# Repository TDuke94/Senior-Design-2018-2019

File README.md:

# Senior-Design-2018-2019
UCF ECE Department Senior Design Group 12

Group Members:
  Fredlin Durand
  Timothy Duke
  Daniel Gutierrez
  Linnette Martinez

This is the code and code issue repository for our Senior Design Project

The goal of this project is the development and prototype implementation of IMU based motion tracking system.

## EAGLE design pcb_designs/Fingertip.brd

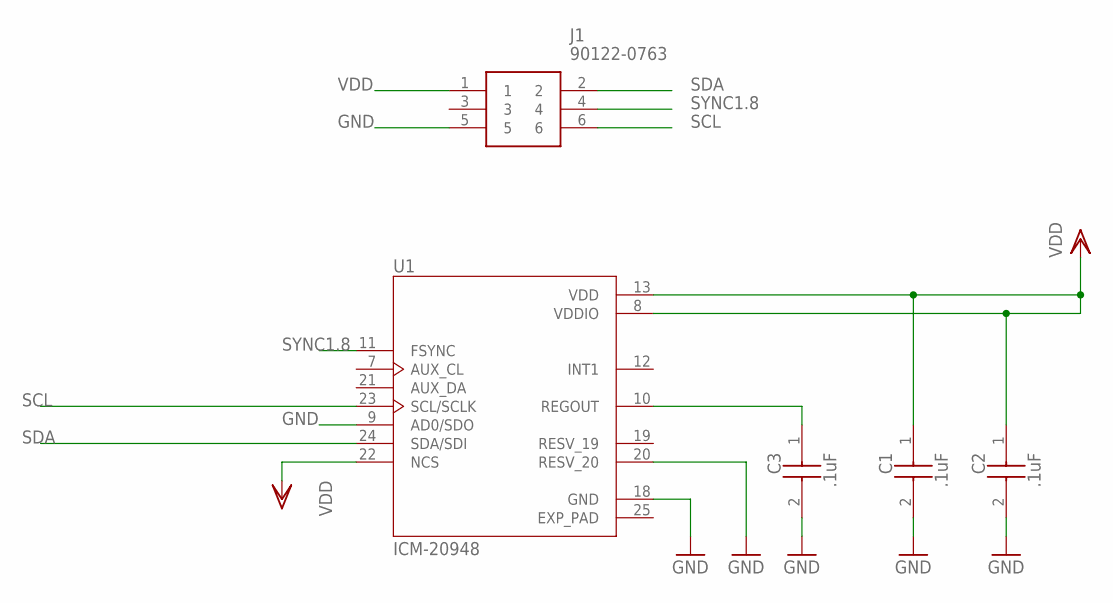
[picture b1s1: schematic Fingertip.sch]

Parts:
C1, C2, C3: .1uF; CAPC2012X88N
J1: 90122-0763; SHDR6W90P254_2X3_762X605X684P
U1: ICM-20948; QFN40P300X300X105-25N

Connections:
EXP_PAD: U1.25 (EXP_PAD)
GND: C1.2, C2.2, C3.2, J1.5, U1.9 (AD0/SDO), U1.18 (GND), U1.20 (RESV_20)
unnamed: C3.1, U1.10 (REGOUT)
SCL: J1.6, U1.23 (SCL/SCLK)
SDA: J1.2, U1.24 (SDA/SDI)
SYNC1.8: J1.4, U1.11 (FSYNC)
VDD: C1.1, C2.1, J1.1, U1.8 (VDDIO), U1.13 (VDD), U1.22 (NCS)

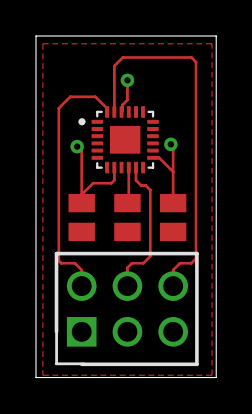
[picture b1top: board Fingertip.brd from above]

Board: 2 copper layers, 10.0 x 19.0 mm, 5 parts (0 on the bottom side), 6 nets.

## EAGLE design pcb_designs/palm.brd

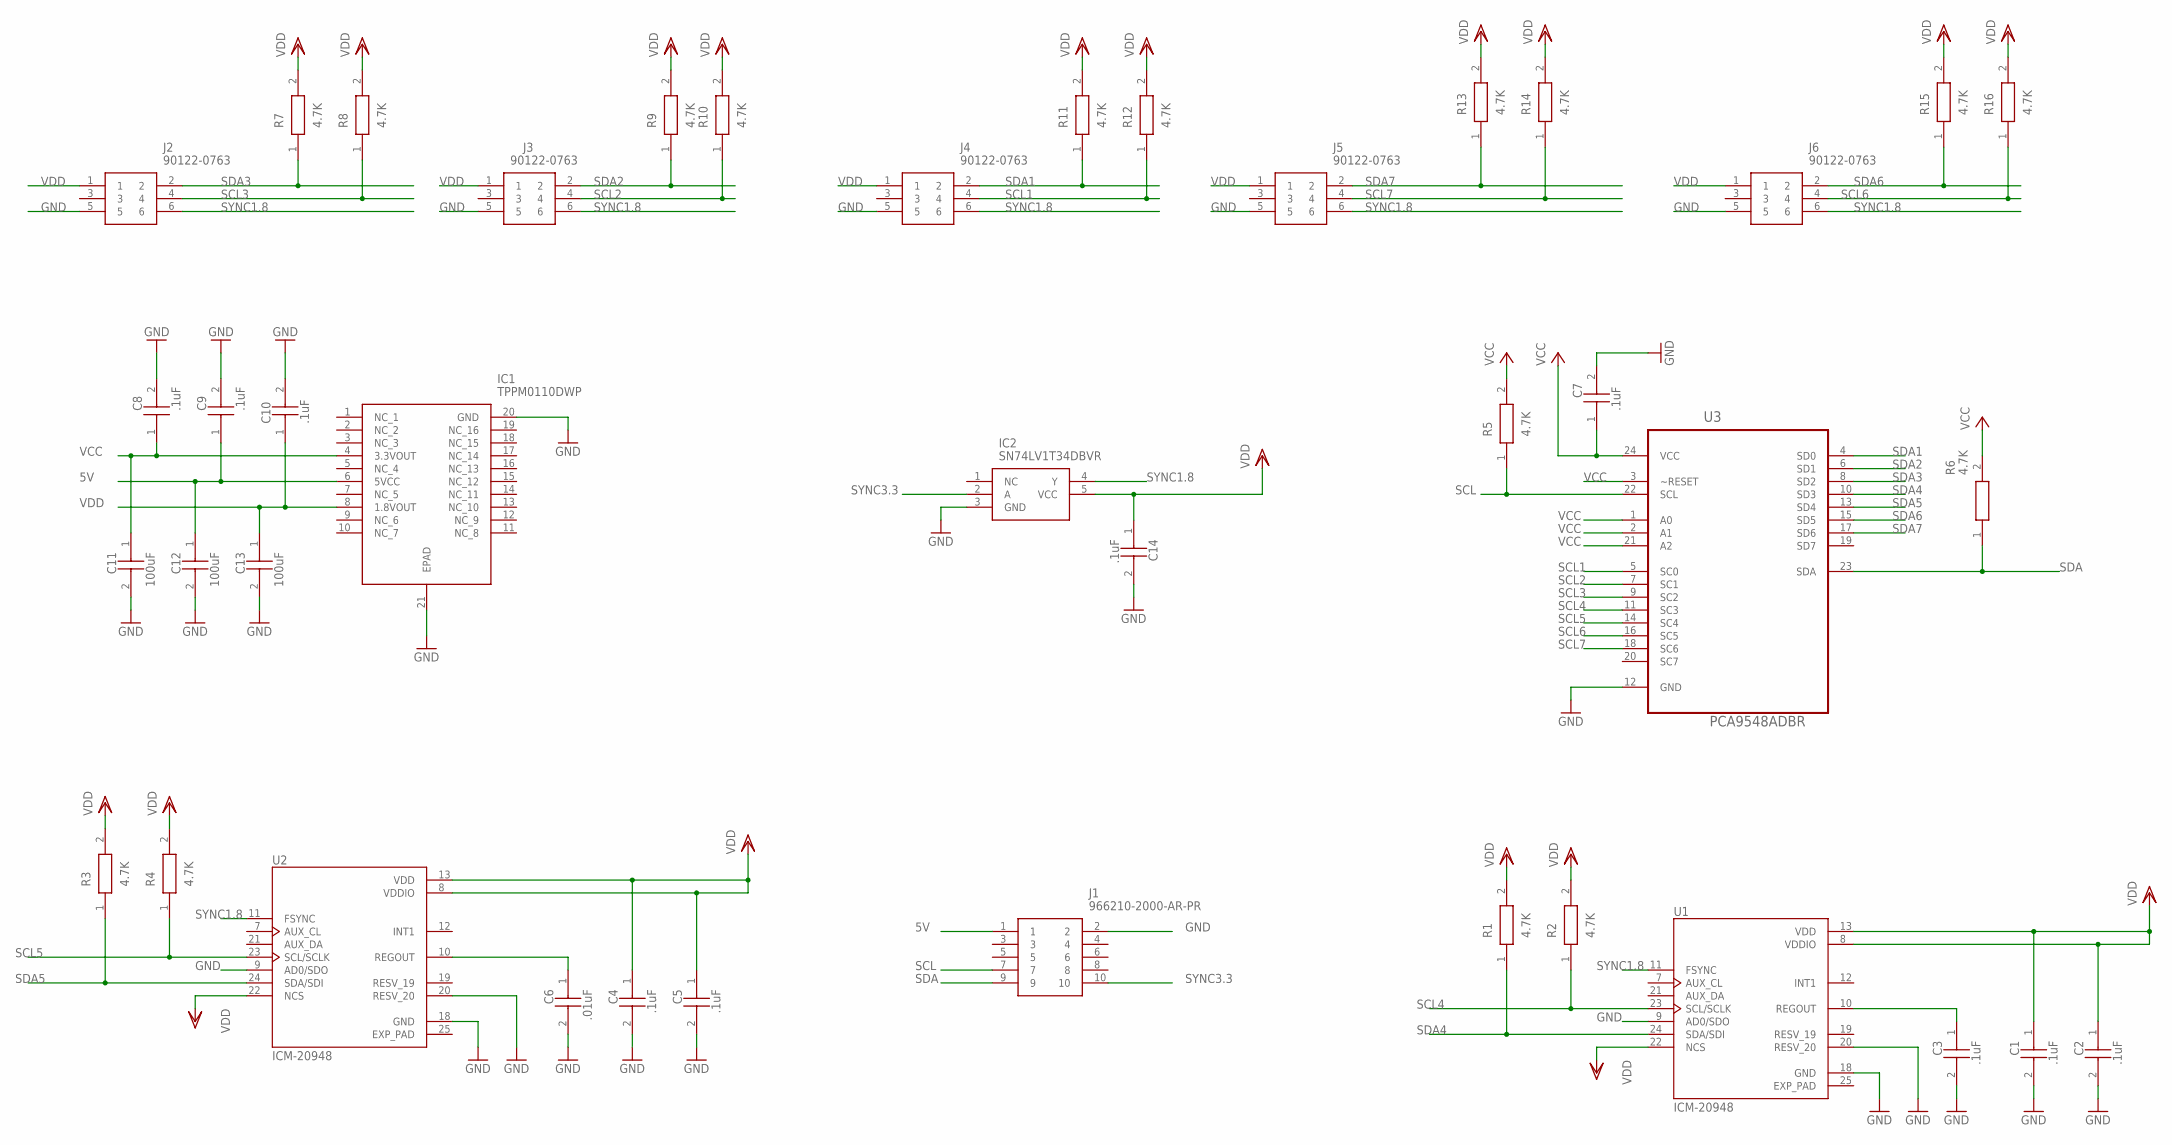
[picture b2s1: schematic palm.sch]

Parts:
C1, C2, C3, C4, C5, C7, C8, C9, C10, C14: .1uF; CAPC2012X88N
C6: .01uF; CAPC2012X88N
C11, C12, C13: 100uF; CAPC3225X279N
IC1: TPPM0110DWP; SOIC127P1040X265-21N
IC2: SN74LV1T34DBVR; SOT95P280X145-5N
J1: 966210-2000-AR-PR
J2, J3, J4, J5, J6: 90122-0763; SHDR6W90P254_2X3_762X605X684P
R1, R2, R3, R4, R5, R6, R7, R8, R9, R10, R11, R12, R13, R14, R15, R16: 4.7K; RESC3216X60N
U1, U2: ICM-20948; QFN40P300X300X105-25N
U3: PCA9548ADBR; SOP65P780X200-24N

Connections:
5V: C9.1, C12.1 (C1), IC1.6 (5VCC), J1.1
EXP_PAD: U1.25 (EXP_PAD), U2.25 (EXP_PAD)
GND: C1.2, C2.2, C3.2, C4.2, C5.2, C6.2, C7.2, C8.2, C9.2, C10.2, C11.2 (C2), C12.2 (C2), C13.2 (C2), C14.2, IC1.20 (GND), IC1.21 (EPAD), IC2.3 (GND), J1.2, J2.5, J3.5, J4.5, J5.5, J6.5, U1.9 (AD0/SDO), U1.18 (GND), U1.20 (RESV_20), U2.9 (AD0/SDO), U2.18 (GND), U2.20 (RESV_20), U3.12 (GND)
unnamed: C6.1, U2.10 (REGOUT)
unnamed: C3.1, U1.10 (REGOUT)
SCL: J1.7, R5.1, U3.22 (SCL)
SCL1: J4.4, R12.1, U3.5 (SC0)
SCL2: J3.4, R10.1, U3.7 (SC1)
SCL3: J2.4, R8.1, U3.9 (SC2)
SCL4: R2.1, U1.23 (SCL/SCLK), U3.11 (SC3)
SCL5: R4.1, U2.23 (SCL/SCLK), U3.14 (SC4)
SCL6: J6.4, R16.1, U3.16 (SC5)
SCL7: J5.4, R14.1, U3.18 (SC6)
SDA: J1.9, R6.1, U3.23 (SDA)
SDA1: J4.2, R11.1, U3.4 (SD0)
SDA2: J3.2, R9.1, U3.6 (SD1)
SDA3: J2.2, R7.1, U3.8 (SD2)
SDA4: R1.1, U1.24 (SDA/SDI), U3.10 (SD3)
SDA5: R3.1, U2.24 (SDA/SDI), U3.13 (SD4)
SDA6: J6.2, R15.1, U3.15 (SD5)
SDA7: J5.2, R13.1, U3.17 (SD6)
SYNC1.8: IC2.4 (Y), J2.6, J3.6, J4.6, J5.6, J6.6, U1.11 (FSYNC), U2.11 (FSYNC)
SYNC3.3: IC2.2 (A), J1.10
VCC: C7.1, C8.1, C11.1 (C1), IC1.4 (3.3VOUT), R5.2, R6.2, U3.1 (A0), U3.2 (A1), U3.3 (~RESET), U3.21 (A2), U3.24 (VCC)
VDD: C1.1, C2.1, C4.1, C5.1, C10.1, C13.1 (C1), C14.1, IC1.8 (1.8VOUT), IC2.5 (VCC), J2.1, J3.1, J4.1, J5.1, J6.1, R1.2, R2.2, R3.2, R4.2, R7.2, R8.2, R9.2, R10.2, R11.2, R12.2, R13.2, R14.2, R15.2, R16.2, U1.8 (VDDIO), U1.13 (VDD), U1.22 (NCS), U2.8 (VDDIO), U2.13 (VDD), U2.22 (NCS)

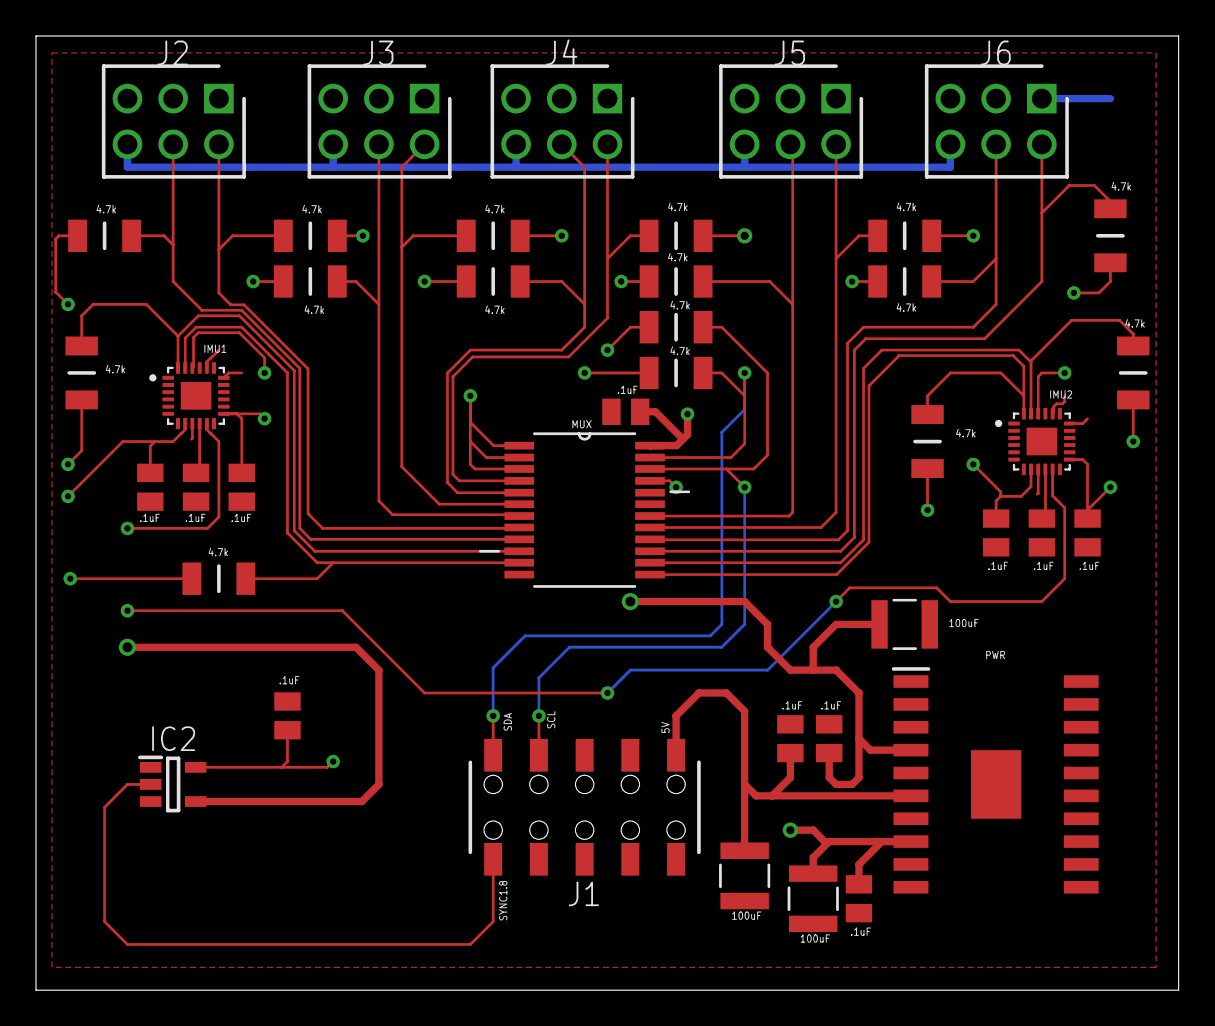
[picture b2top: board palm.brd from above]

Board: 2 copper layers, 63.5 x 53.0 mm, 41 parts (0 on the bottom side), 25 nets.

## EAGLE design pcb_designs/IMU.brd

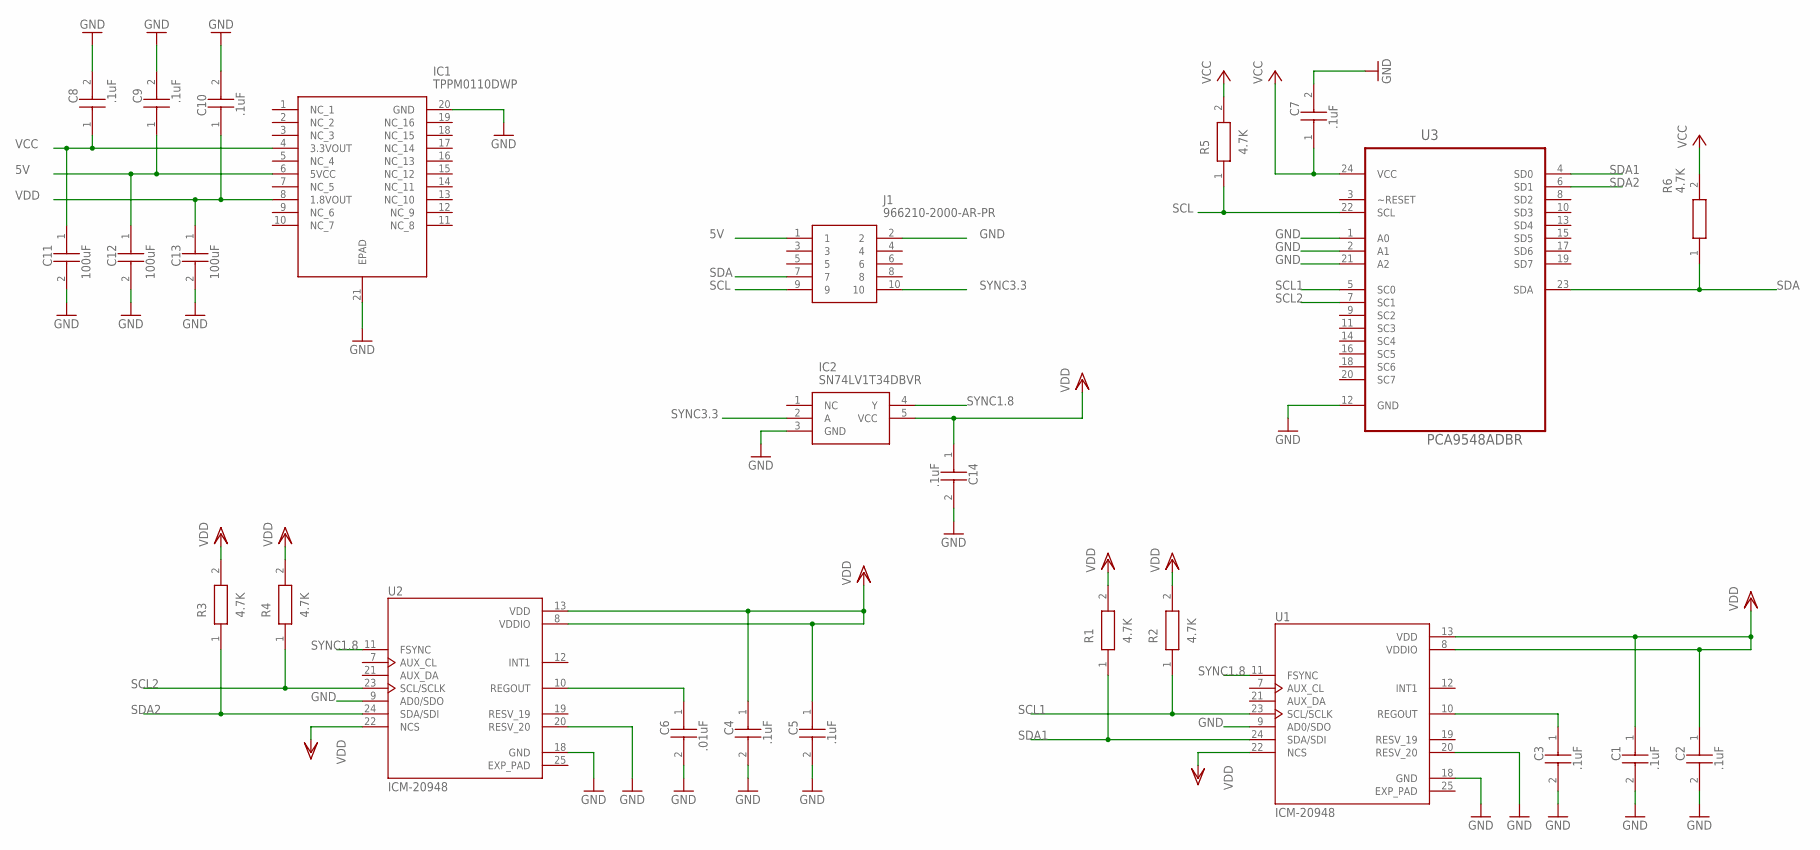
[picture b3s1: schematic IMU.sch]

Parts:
C1, C2, C3, C4, C5, C7, C8, C9, C10, C14: .1uF; CAPC2012X88N
C6: .01uF; CAPC2012X88N
C11, C12, C13: 100uF; CAPC3225X279N
IC1: TPPM0110DWP; SOIC127P1040X265-21N
IC2: SN74LV1T34DBVR; SOT95P280X145-5N
J1: 966210-2000-AR-PR
R1, R2, R3, R4, R5, R6: 4.7K; RESC3216X60N
U1, U2: ICM-20948; QFN40P300X300X105-25N
U3: PCA9548ADBR; SOP65P780X200-24N

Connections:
5V: C9.1, C12.1 (C1), IC1.6 (5VCC), J1.1
EXP_PAD: U1.25 (EXP_PAD), U2.25 (EXP_PAD)
GND: C1.2, C2.2, C3.2, C4.2, C5.2, C6.2, C7.2, C8.2, C9.2, C10.2, C11.2 (C2), C12.2 (C2), C13.2 (C2), C14.2, IC1.20 (GND), IC1.21 (EPAD), IC2.3 (GND), J1.2, U1.9 (AD0/SDO), U1.18 (GND), U1.20 (RESV_20), U2.9 (AD0/SDO), U2.18 (GND), U2.20 (RESV_20), U3.1 (A0), U3.2 (A1), U3.12 (GND), U3.21 (A2)
unnamed: C6.1, U2.10 (REGOUT)
unnamed: C3.1, U1.10 (REGOUT)
SCL: J1.9, R5.1, U3.22 (SCL)
SCL1: R2.1, U1.23 (SCL/SCLK), U3.5 (SC0)
SCL2: R4.1, U2.23 (SCL/SCLK), U3.7 (SC1)
SDA: J1.7, R6.1, U3.23 (SDA)
SDA1: R1.1, U1.24 (SDA/SDI), U3.4 (SD0)
SDA2: R3.1, U2.24 (SDA/SDI), U3.6 (SD1)
SYNC1.8: IC2.4 (Y), U1.11 (FSYNC), U2.11 (FSYNC)
SYNC3.3: IC2.2 (A), J1.10
VCC: C7.1, C8.1, C11.1 (C1), IC1.4 (3.3VOUT), R5.2, R6.2, U3.24 (VCC)
VDD: C1.1, C2.1, C4.1, C5.1, C10.1, C13.1 (C1), C14.1, IC1.8 (1.8VOUT), IC2.5 (VCC), R1.2, R2.2, R3.2, R4.2, U1.8 (VDDIO), U1.13 (VDD), U1.22 (NCS), U2.8 (VDDIO), U2.13 (VDD), U2.22 (NCS)

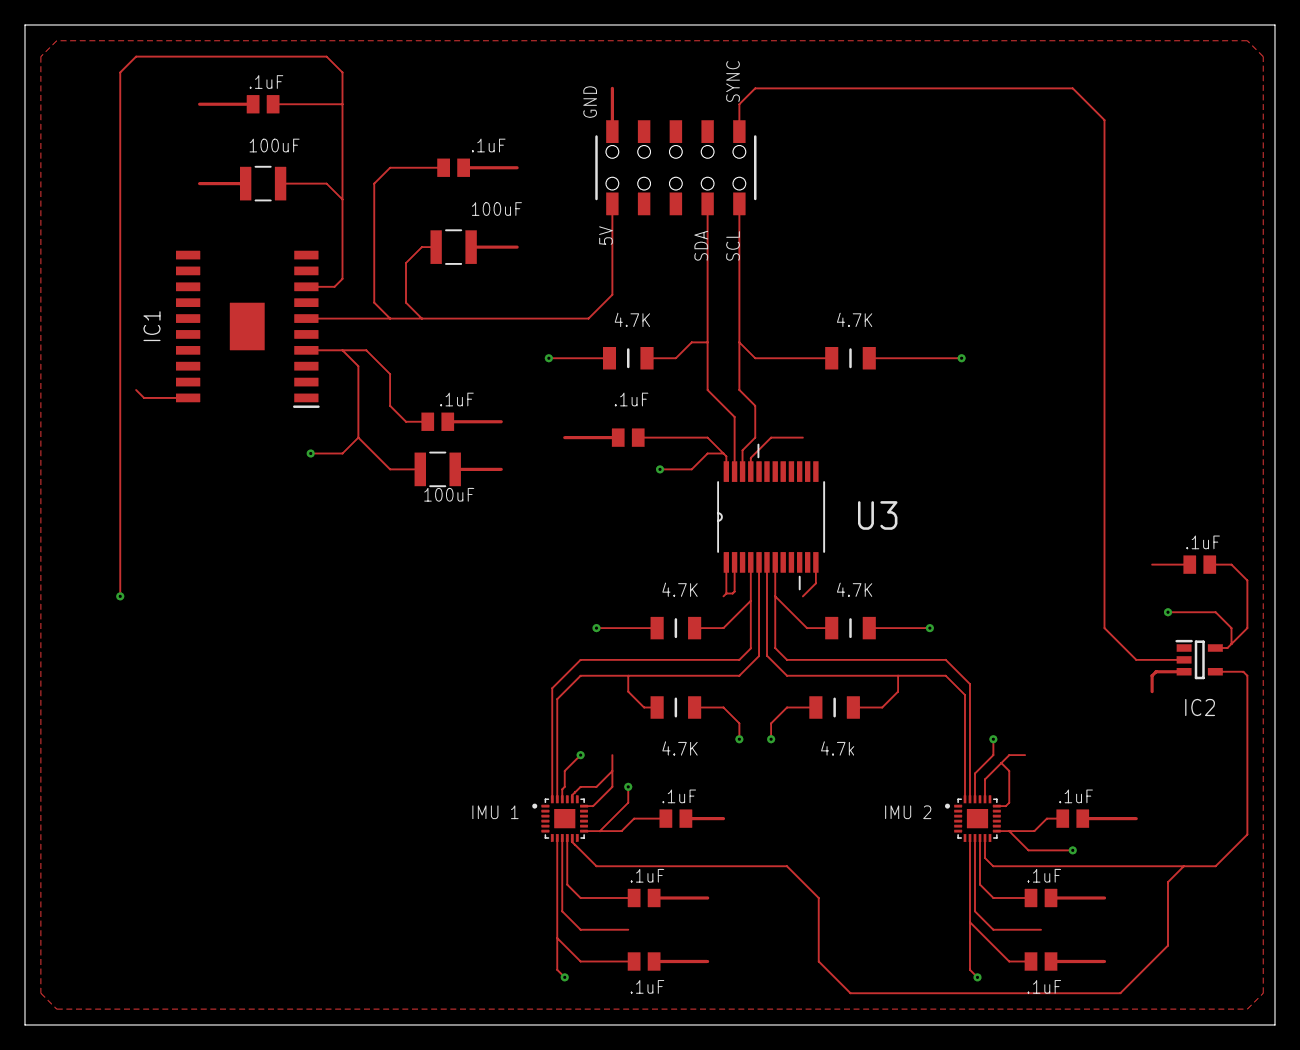
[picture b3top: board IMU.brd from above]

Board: 2 copper layers, 100.0 x 80.0 mm, 26 parts (0 on the bottom side), 15 nets.

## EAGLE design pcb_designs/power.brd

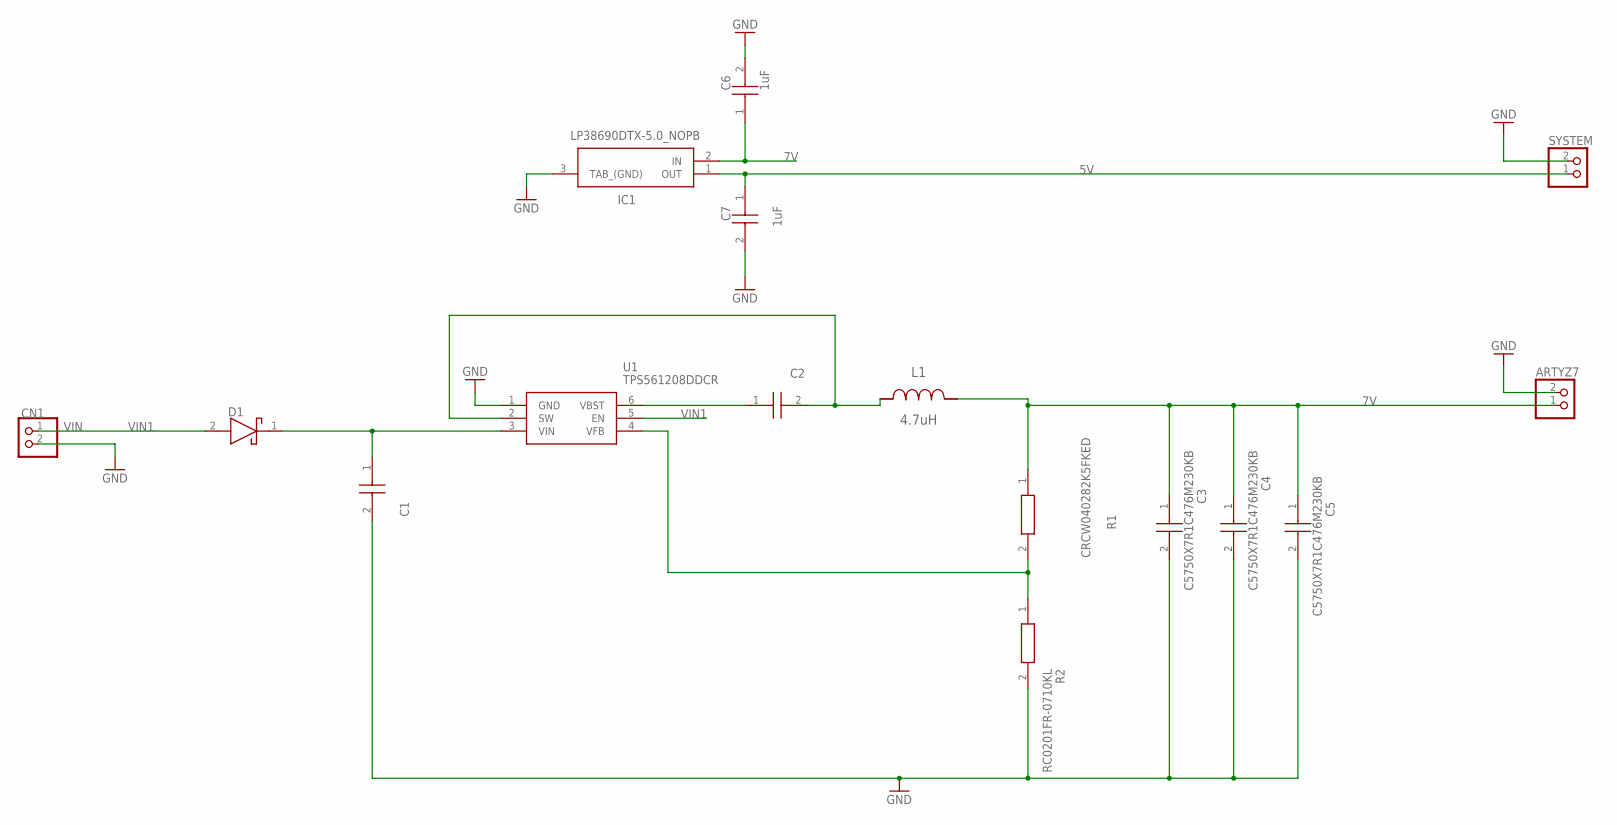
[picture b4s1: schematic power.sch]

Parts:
ARTYZ7: JST_2PIN-SMT-RA; JST-PH-2-SMT-RA
C1: 593D226X9025D2TE3; CAPPM7343X310N
C2: C0603C104Z3VACTU; CAPC1608X90N
C3, C4, C5: C5750X7R1C476M230KB; CAPC5750X250N
C6, C7: 1uF; CAPC1608X80N
CN1: JST_2PIN-SMT-RA; JST-PH-2-SMT-RA
D1: NRVB120VLSFT1G; SODFL3616X98N
IC1: LP38690DTX-5.0_NOPB; LM78M05CDT
L1: 4.7uH; SLF7045
R1: CRCW040282K5FKED; RESC1005X40N
R2: RC0201FR-0710KL; RESC0603X26N
SYSTEM: JST_2PIN-SMT-RA; JST-PH-2-SMT-RA
U1: TPS561208DDCR; SOT95P280X110-6N

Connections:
5V: C7.1, IC1.1 (OUT), SYSTEM.1 (2)
7V: ARTYZ7.1 (2), C3.1, C4.1, C5.1, C6.1, IC1.2 (IN), L1.2, R1.1
GND: ARTYZ7.2 (1), C1.2 (-), C3.2, C4.2, C5.2, C6.2, C7.2, CN1.2 (1), IC1.3 (TAB_(GND)), R2.2, SYSTEM.2 (1), U1.1 (GND)
unnamed: C2.1, U1.6 (VBST)
unnamed: C2.2, L1.1, U1.2 (SW)
unnamed: R1.2, R2.1, U1.4 (VFB)
VIN: CN1.1 (2), D1.2 (A)
VIN1: C1.1 (+), D1.1 (K), U1.3 (VIN), U1.5 (EN)

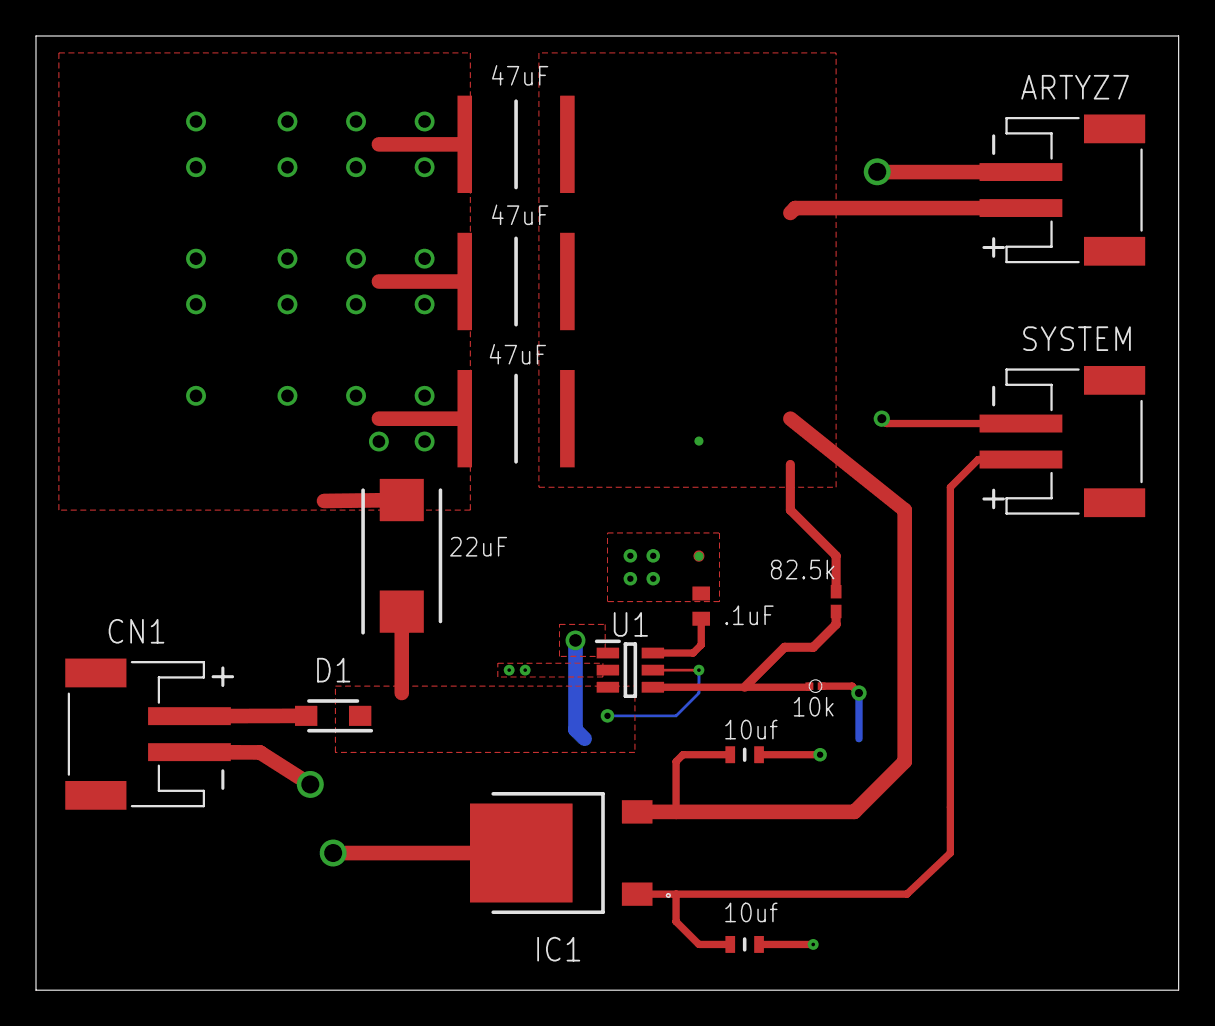
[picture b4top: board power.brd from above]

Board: 2 copper layers, 63.5 x 53.0 mm, 16 parts (0 on the bottom side), 8 nets.

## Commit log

2018-11-14 Upload of SD Card Image
    Upload of the first SD card image to use for initial board testing
2018-11-14 New SD Card Image
2018-12-21 This is some basic code demonstrating the usage of a queue buffer sending data from one task to another
2018-12-21 I2C Initial
    Initial upload of I2C code under development.
2018-12-28 Arty-Z7 Initial Upload
2018-12-28 Queue Test Funcitonal v0
2019-01-14 This is some preliminary code written in C that tries to take data and perform calculations that will provide key data
2019-01-15 Updated Queue Design, Bugs Remain
2019-01-19 This is the early eversion of implementing the math functions that will be used for IMIU Data manipulation.
2019-01-19 ~minor change~
2019-01-19 new Queue Version and I2C on Zynq
2019-01-19 MSP430 I2C update, Talks to Zynq
2019-01-19 Update of Zynq I2C capabilities
2019-01-20 I2C Driver Update
2019-01-23 this update contains a more structured and well defined Math Library that will allow for easier use on Queue Tasks. Code cleanup and comments still needs to be workedd on
2019-02-15 Modified the Math Library Functions in Data Manipulation
2019-02-15 I2C to Zynq Update
2019-03-08 Update with functioning pipeline and SPI (marginal)
2019-03-11 SPI refresh
2019-03-26 Bluetooth/SPI Integration Code Update
2019-03-26 fixing things
2019-03-26 this might have fixed the uploading
2019-03-29 ICM 20948 and pipeline updates
2019-03-29 Physical models from Onshape and 3D models from Maya
2019-03-29 eagle designs
2019-04-02 MSP430 with two IMUs
2019-04-02 SPI code
2019-04-02 SPI and BT updates - slight code clean
2019-04-04 msp forgotten file :'(
2019-04-04 fixing BT comm to support AA filtering from SPI
2019-04-04 SPI filter addition
2019-04-05 i2c update
2019-04-10 uploading the script that manipulates adn evaluates the data in Unity
2019-04-14 Embedded Code, Semi-Final
2019-04-14 updating unity scripts
2019-04-14 all of what we need to run this on unity
